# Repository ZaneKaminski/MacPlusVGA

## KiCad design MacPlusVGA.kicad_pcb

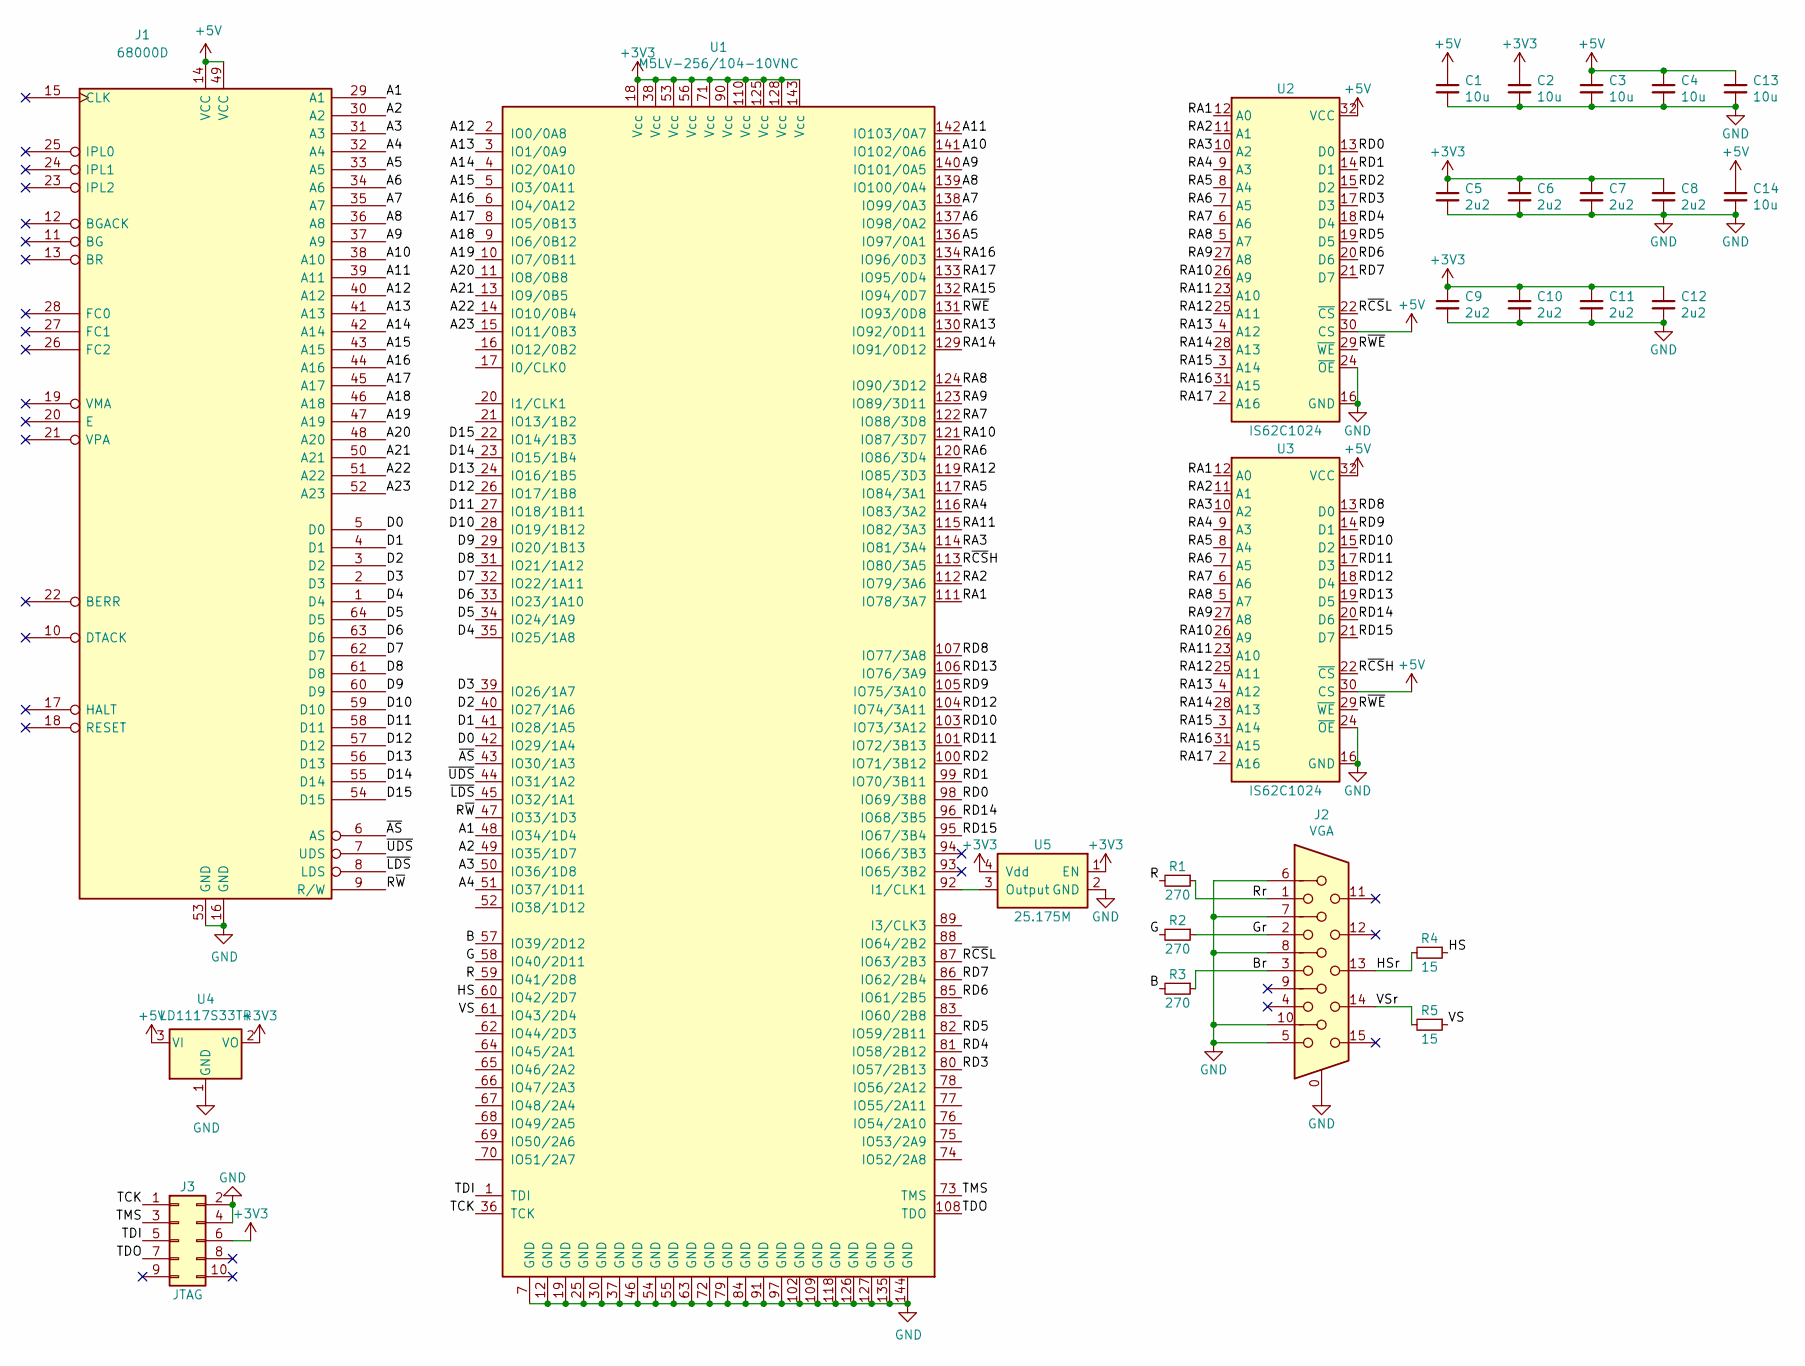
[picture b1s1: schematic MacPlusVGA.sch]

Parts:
C1, C2, C3, C4, C13, C14: 10u; C_0805
C5, C6, C7, C8, C9, C10, C11, C12: 2u2; C_0603
J1: 68000D; DIP-64-Slot
J2: VGA; DSUB-15-HD_Female_Horizontal_P2.29x1.98mm_EdgePinOffset3.03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
J3: JTAG; IDC_SMD_2x05_P2.54mm_Vertical
R1, R2, R3: 270; R_0805
R4, R5: 15; R_0805
U1: M5LV-256/104-10VNC; TQFP-144_20x20mm_P0.5mm
U2, U3: IS62C1024; SOP-32_P1.27mm
U4: LD1117S33TR; SOT-223
U5: 25.175M; Crystal_SMD_3225-4Pin_3.2x2.5mm

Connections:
+3V3: C2.1, C5.1, C6.1, C7.1, C8.1, C9.1, C10.1, C11.1, C12.1, J3.6, U1.18 (Vcc), U1.38 (Vcc), U1.53 (Vcc), U1.56 (Vcc), U1.71 (Vcc), U1.90 (Vcc), U1.110 (Vcc), U1.125 (Vcc), U1.128 (Vcc), U1.143 (Vcc), U4.2 (VO), U5.1 (EN), U5.4 (Vdd)
+5V: C1.1, C3.1, C4.1, C13.1, C14.1, J1.14 (VCC), J1.49 (VCC), U2.30 (CS), U2.32 (VCC), U3.30 (CS), U3.32 (VCC), U4.3 (VI)
/A1: J1.29 (A1), U1.48 (IO34/1D4)
/A2: J1.30 (A2), U1.49 (IO35/1D7)
/A3: J1.31 (A3), U1.50 (IO36/1D8)
/A4: J1.32 (A4), U1.51 (IO37/1D11)
/A5: J1.33 (A5), U1.136 (IO97/0A1)
/A6: J1.34 (A6), U1.137 (IO98/0A2)
/A7: J1.35 (A7), U1.138 (IO99/0A3)
/A8: J1.36 (A8), U1.139 (IO100/0A4)
/A9: J1.37 (A9), U1.140 (IO101/0A5)
/A10: J1.38 (A10), U1.141 (IO102/0A6)
/A11: J1.39 (A11), U1.142 (IO103/0A7)
/A12: J1.40 (A12), U1.2 (IO0/0A8)
/A13: J1.41 (A13), U1.3 (IO1/0A9)
/A14: J1.42 (A14), U1.4 (IO2/0A10)
/A15: J1.43 (A15), U1.5 (IO3/0A11)
/A16: J1.44 (A16), U1.6 (IO4/0A12)
/A17: J1.45 (A17), U1.8 (IO5/0B13)
/A18: J1.46 (A18), U1.9 (IO6/0B12)
/A19: J1.47 (A19), U1.10 (IO7/0B11)
/A20: J1.48 (A20), U1.11 (IO8/0B8)
/A21: J1.50 (A21), U1.13 (IO9/0B5)
/A22: J1.51 (A22), U1.14 (IO10/0B4)
/A23: J1.52 (A23), U1.15 (IO11/0B3)
/B: R3.2, U1.57 (IO39/2D12)
/Br: J2.3, R3.1
/D0: J1.5 (D0), U1.42 (IO29/1A4)
/D1: J1.4 (D1), U1.41 (IO28/1A5)
/D2: J1.3 (D2), U1.40 (IO27/1A6)
/D3: J1.2 (D3), U1.39 (IO26/1A7)
/D4: J1.1 (D4), U1.35 (IO25/1A8)
/D5: J1.64 (D5), U1.34 (IO24/1A9)
/D6: J1.63 (D6), U1.33 (IO23/1A10)
/D7: J1.62 (D7), U1.32 (IO22/1A11)
/D8: J1.61 (D8), U1.31 (IO21/1A12)
/D9: J1.60 (D9), U1.29 (IO20/1B13)
/D10: J1.59 (D10), U1.28 (IO19/1B12)
/D11: J1.58 (D11), U1.27 (IO18/1B11)
/D12: J1.57 (D12), U1.26 (IO17/1B8)
/D13: J1.56 (D13), U1.24 (IO16/1B5)
/D14: J1.55 (D14), U1.23 (IO15/1B4)
/D15: J1.54 (D15), U1.22 (IO14/1B3)
/G: R2.2, U1.58 (IO40/2D11)
/Gr: J2.2, R2.1
/HS: R4.1, U1.60 (IO42/2D7)
/HSr: J2.13, R4.2
/R: R1.2, U1.59 (IO41/2D8)
/RA1: U1.111 (IO78/3A7), U2.12 (A0), U3.12 (A0)
/RA2: U1.112 (IO79/3A6), U2.11 (A1), U3.11 (A1)
/RA3: U1.114 (IO81/3A4), U2.10 (A2), U3.10 (A2)
/RA4: U1.116 (IO83/3A2), U2.9 (A3), U3.9 (A3)
/RA5: U1.117 (IO84/3A1), U2.8 (A4), U3.8 (A4)
/RA6: U1.120 (IO86/3D4), U2.7 (A5), U3.7 (A5)
/RA7: U1.122 (IO88/3D8), U2.6 (A6), U3.6 (A6)
/RA8: U1.124 (IO90/3D12), U2.5 (A7), U3.5 (A7)
/RA9: U1.123 (IO89/3D11), U2.27 (A8), U3.27 (A8)
/RA10: U1.121 (IO87/3D7), U2.26 (A9), U3.26 (A9)
/RA11: U1.115 (IO82/3A3), U2.23 (A10), U3.23 (A10)
/RA12: U1.119 (IO85/3D3), U2.25 (A11), U3.25 (A11)
/RA13: U1.130 (IO92/0D11), U2.4 (A12), U3.4 (A12)
/RA14: U1.129 (IO91/0D12), U2.28 (A13), U3.28 (A13)
/RA15: U1.132 (IO94/0D7), U2.3 (A14), U3.3 (A14)
/RA16: U1.134 (IO96/0D3), U2.31 (A15), U3.31 (A15)
/RA17: U1.133 (IO95/0D4), U2.2 (A16), U3.2 (A16)
/RD0: U1.98 (IO69/3B8), U2.13 (D0)
/RD1: U1.99 (IO70/3B11), U2.14 (D1)
/RD2: U1.100 (IO71/3B12), U2.15 (D2)
/RD3: U1.80 (IO57/2B13), U2.17 (D3)
/RD4: U1.81 (IO58/2B12), U2.18 (D4)
/RD5: U1.82 (IO59/2B11), U2.19 (D5)
/RD6: U1.85 (IO61/2B5), U2.20 (D6)
/RD7: U1.86 (IO62/2B4), U2.21 (D7)
/RD8: U1.107 (IO77/3A8), U3.13 (D0)
/RD9: U1.105 (IO75/3A10), U3.14 (D1)
/RD10: U1.103 (IO73/3A12), U3.15 (D2)
/RD11: U1.101 (IO72/3B13), U3.17 (D3)
/RD12: U1.104 (IO74/3A11), U3.18 (D4)
/RD13: U1.106 (IO76/3A9), U3.19 (D5)
/RD14: U1.96 (IO68/3B5), U3.20 (D6)
/RD15: U1.95 (IO67/3B4), U3.21 (D7)
/Rr: J2.1, R1.1
/R~CS~H: U1.113 (IO80/3A5), U3.22 (~CS~)
/R~CS~L: U1.87 (IO63/2B3), U2.22 (~CS~)
/R~WE~: U1.131 (IO93/0D8), U2.29 (~WE), U3.29 (~WE)
/R~W~: J1.9 (R/W), U1.47 (IO33/1D3)
/TCK: J3.1, U1.36 (TCK)
/TDI: J3.5, U1.1 (TDI)
/TDO: J3.7, U1.108 (TDO)
/TMS: J3.3, U1.73 (TMS)
/VS: R5.1, U1.61 (IO43/2D4)
/VSr: J2.14, R5.2
/~AS~: J1.6 (AS), U1.43 (IO30/1A3)
/~LDS~: J1.8 (LDS), U1.45 (IO32/1A1)
/~UDS~: J1.7 (UDS), U1.44 (IO31/1A2)
GND: C1.2, C2.2, C3.2, C4.2, C5.2, C6.2, C7.2, C8.2, C9.2, C10.2, C11.2, C12.2, C13.2, C14.2, J1.16 (GND), J1.53 (GND), J2.0, J2.5, J2.6, J2.7, J2.8, J2.10, J3.2, J3.4, U1.7 (GND), U1.12 (GND), U1.19 (GND), U1.25 (GND), U1.30 (GND), U1.37 (GND), U1.46 (GND), U1.54 (GND), U1.55 (GND), U1.63 (GND), U1.72 (GND), U1.79 (GND), U1.84 (GND), U1.91 (GND), U1.97 (GND), U1.102 (GND), U1.109 (GND), U1.118 (GND), U1.126 (GND), U1.127 (GND), U1.135 (GND), U1.144 (GND), U2.16 (GND), U2.24 (~OE), U3.16 (GND), U3.24 (~OE), U4.1 (GND), U5.2 (GND)
unnamed: U1.92 (I1/CLK1), U5.3 (Output)

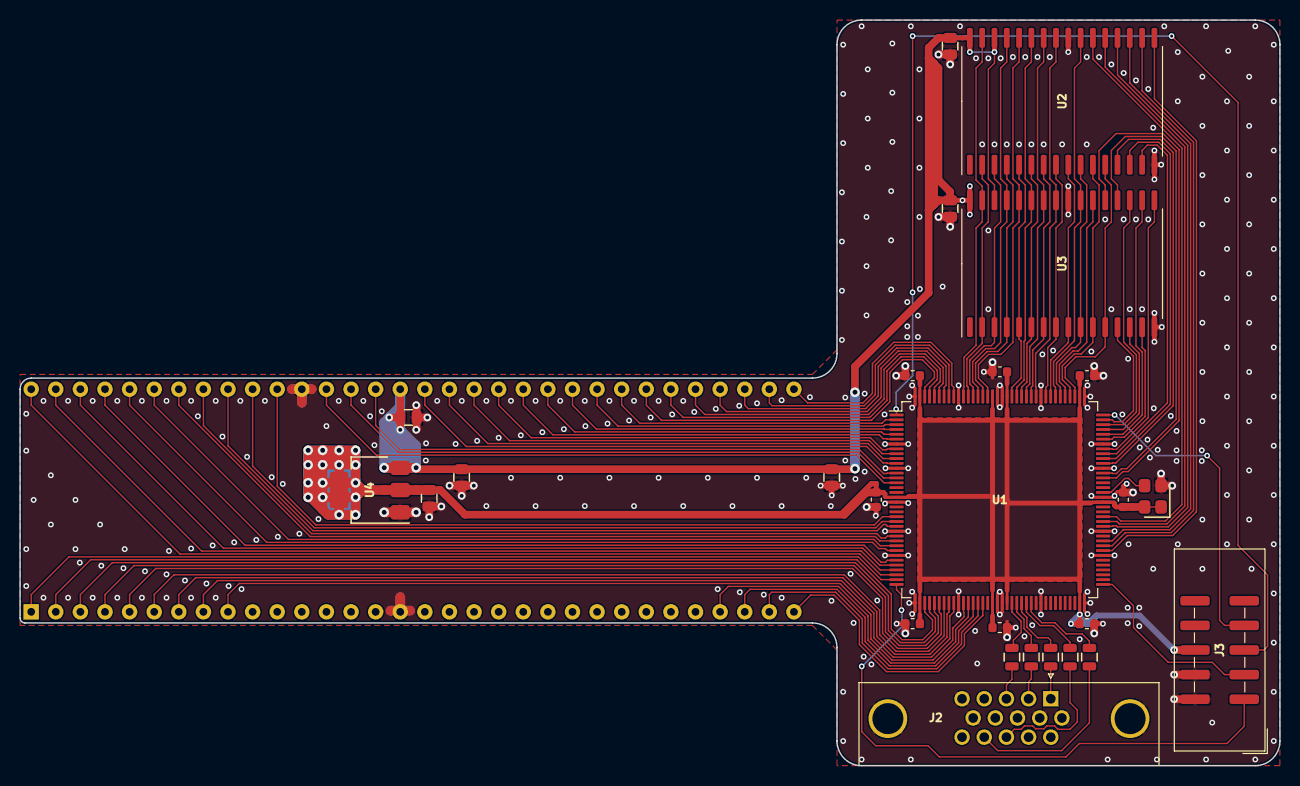
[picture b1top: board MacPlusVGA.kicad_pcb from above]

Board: 2 copper layers, 130.0 x 77.0 mm, 27 parts (0 on the bottom side), 97 nets.

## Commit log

2020-06-05 Begun
2020-07-02 Board done? Needs some cleanup though
2020-07-02 More verilog but some bugs left to fix
2020-07-06 As sent to JLCPCB July 2020
